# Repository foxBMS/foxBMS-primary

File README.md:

# foxBMS 

foxBMS is a free, open and flexible development environment to design battery
management systems. It is the first modular open source BMS development
platform.

## foxBMS Project Setup
The foxBMS project consists of several repositories.

The foxConda-installer repository contains the installer for the foxConda
environment. This environment provides all the tools necessary to generate the
documentation, compile the code for the MCUs and flash the generated binaries on
the MCUs (e.g., Python, git, GCC).

The starting point to get foxBMS is the foxBMS-setup
repository (https://github.com/foxBMS/foxBMS-setup), which contains
the general setup files for the foxBMS project. It includes a setup script
(bootstrap.py) which clones all the other needed repositories. The needed
documentation will be generated automatically after these repositories have been
cloned. The generated documentation is found in the directory ./build.
After the bootstrap step, the top project directory (foxBMS-setup) structure
looks like this:

 - foxBMS-setup <dir>
  - .git <dir> *
  - build <dir>
  - foxBMS-documentation <dir>
  - foxBMS-hardware <dir>
  - foxBMS-primary <dir>
  - foxBMS-secondary <dir>
  - foxBMS-tools <dir>
  - FreeRTOS <dir>
  - hal <dir>
  - .gitignore <file> *
  - bootstrap.py <file>
  - build.py <file>
  - CHANGELOG.md <file>
  - clean.py <file>
  - LICENSE.md <file>
  - README.md <file>
  - wscript <file>

* Directories and files with starting full stop are hidden in Windows in default
configuration.

There is a help available by running "python bootstrap.py -h".

## foxBMS Repositories

The foxConda-installer and foxBMS-setup repositories have already been described.

foxBMS is made out of two Microcontroller Units (MCU), named primary and
secondary. The C code for the primary MCU is found in the repository
foxBMS-primary (https://github.com/foxBMS/foxBMS-primary). The C code for the
secondary MCU is found in the repository foxBMS-secondary
(https://github.com/foxBMS/foxBMS-secondary). The Doxygen documentation is
generated from these sources into ./build/primary/doxygen/html and
./build/secondary/doxygen/html respectively. The main file is in both cases
index.html.

The layout and schematic files for the foxBMS hardware are found in the
foxBMS-hardware repository (https://github.com/foxBMS/foxBMS-hardware).

The Hardware Abstraction Layer (hal) for foxBMS is found in the hal-repository
(https://github.com/foxBMS/hal.) The real time operating system (FreeRTOS) for
foxBMS is found in the FreeRTOS-repository (https://github.com/foxBMS/FreeRTOS.)

The tools needed for foxBMS are in the foxBMS-tools-repository
(https://github.com/foxBMS/foxBMS-tools.)

The general documentation files for the foxBMS project are found in the
foxBMS-documentation repository
(https://github.com/foxBMS/foxBMS-documentation). The sphinx documentation is
found in foxBMS-documentation/doc/sphinx while the Doxygen documentation
configuration is found in foxBMS-documentation/doc/doxygen. The Doxygen
documentation itself is found in the software sources of the primary and
secondary microcontroller. The general documentation, rendered from the sphinx
sources is found in ./build/sphinx/foxBMS-documentation/doc/sphinx/html. The
main file is index.html

A generated version of the Sphinx documentation can be found at
http://foxbms.readthedocs.io/. It explains the structure of the
foxBMS hardware, how to install the foxConda environment and how to use foxConda
to compile and flash the sources.

## Building the Sources
For building the software, open a shell and type "python build.py -h". All
available build options will be displayed. The top build directory is ./build.

## Cleaning the ./build-Directory
For cleaning instructions open a shell and type "python clean.py -h". All
available cleaning options will be displayed.

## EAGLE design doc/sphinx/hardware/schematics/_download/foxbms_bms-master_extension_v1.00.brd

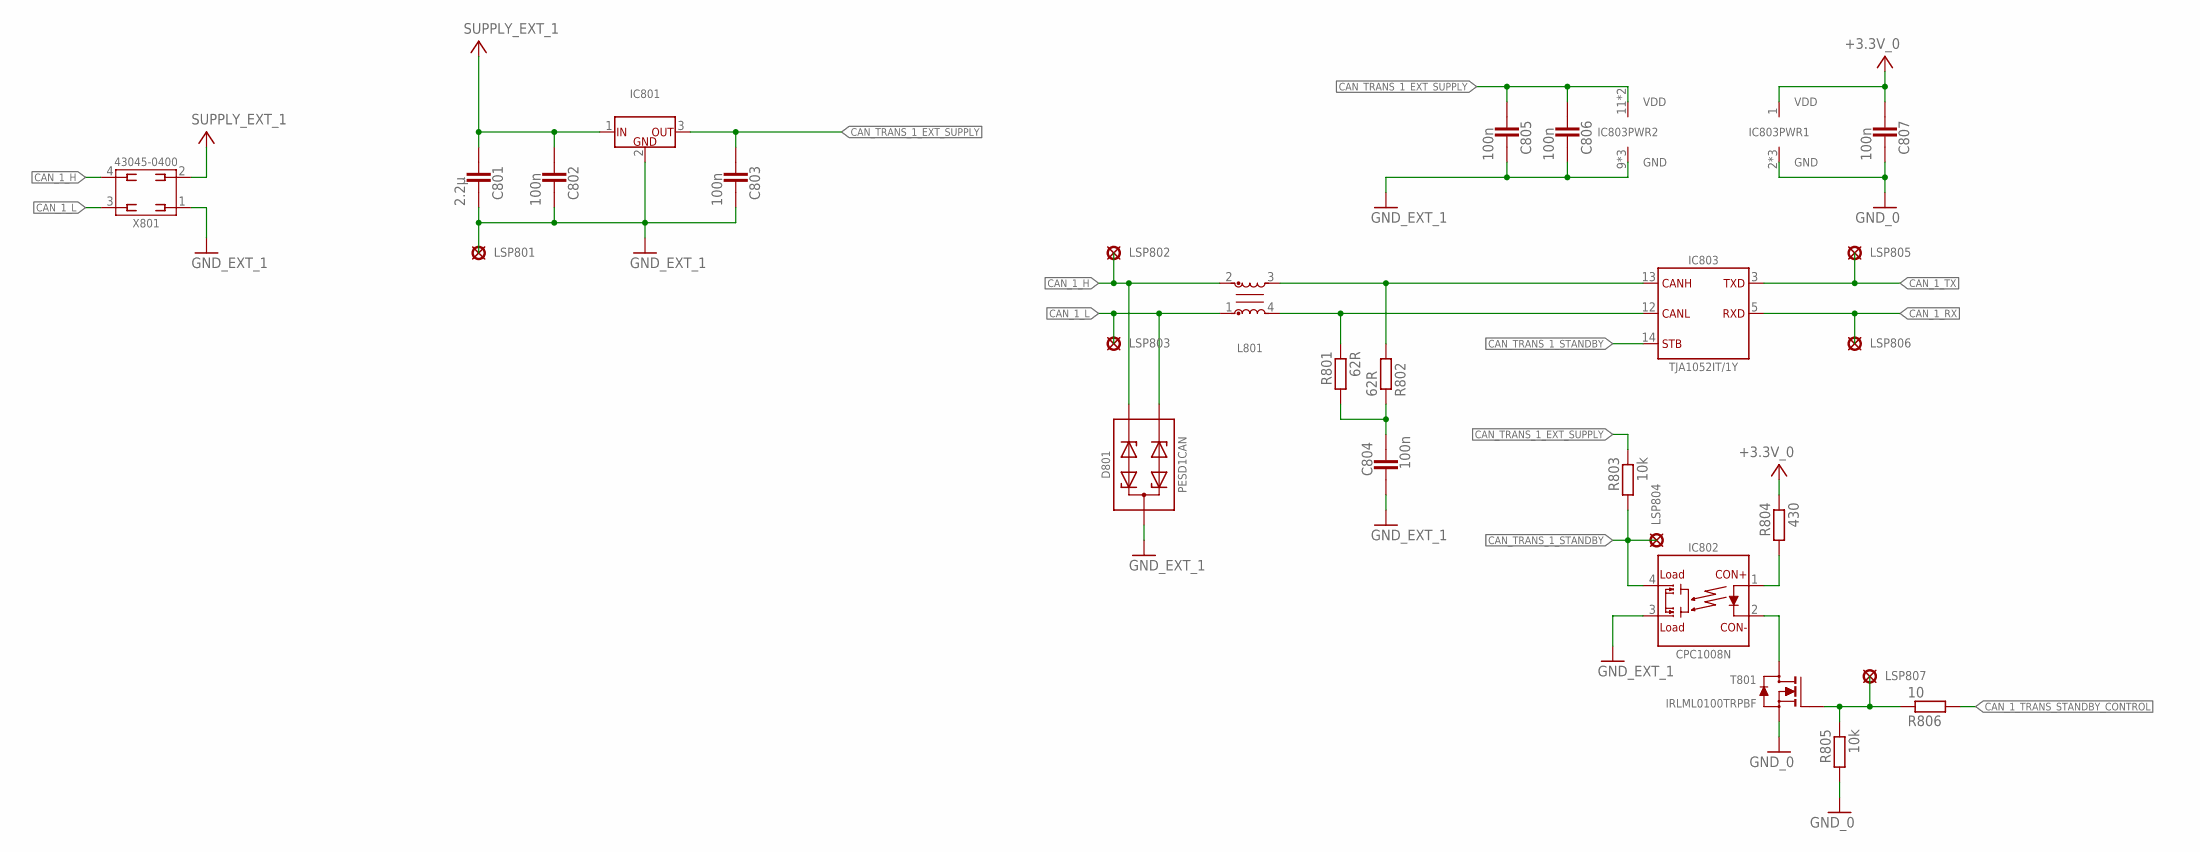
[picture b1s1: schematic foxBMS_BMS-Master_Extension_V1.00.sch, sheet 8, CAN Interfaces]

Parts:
C801: 2.2µ; 0603
C802, C803, C804, C805, C806, C807: 100n; 0603
D801: PESD1CAN; D_SMD_SOT23_(TO-236AB)_R_NXP_REV01
IC801: KA7805ERTF; IC_SMD_TO-252_(D-PAK)_R_FAIRCHILD_REV01
IC802: CPC1008N; K_SMD_SOP-4_R_IXYS_REV01
IC803: TJA1052IT/1Y; IC_SMD_SO16_(SOT162-1)_R_NXP_REV01
L801: B82789C0513N002; L_SMD_FILTER_HF_R_EPCOS_SIMDAD_1812_REV01
LSP801, LSP802, LSP803, LSP804, LSP805, LSP806, LSP807: PAD_2.0X1.5MM; PAD2.0X1.5MM
R801, R802: 62R; 0603
R803, R805: 10k; 0603
R804: 430; 0603
R806: 10; 0603
T801: IRLML0100TRPBF; V_SMD_SOT-23_(TO-236AB)_R_IR_REV01
X801: 43045-0400_MOLEX_4PIN; X_TH_MOLEX_43045-0400_R_REV01

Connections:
+3.3V_0: C807.2, IC803.1 (VDD), R804.1; also elsewhere on the board
CAN_1_H: D801.1, L801.2, LSP802.P$1, X801.4
CAN_1_L: D801.2, L801.1, LSP803.P$1, X801.3
CAN_1_RX: IC803.5 (RXD), LSP806.P$1; also elsewhere on the board
CAN_1_TRANS_STANDBY_CONTROL: R806.2; also elsewhere on the board
CAN_1_TX: IC803.3 (TXD), LSP805.P$1; also elsewhere on the board
CAN_L_INT1: IC803.12 (CANL), L801.4, R801.1
CAN_SPLIT1: C804.1, R801.2, R802.1
CAN_TRANS_1_EXT_SUPPLY: C803.2, C805.2, C806.2, IC801.3 (OUT), IC803.11 (VDD), IC803.16 (VDD), R803.1
CAN_TRANS_1_STANDBY: IC802.4, IC803.14 (STB), LSP804.P$1, R803.2
GND_0: C807.1, IC803.2 (GND), IC803.7 (GND), IC803.8 (GND), R805.2, T801.2 (S); also elsewhere on the board
GND_EXT_1: C801.1, C802.1, C803.1, C804.2, C805.1, C806.1, D801.3, IC801.2 (GND), IC802.3, IC803.9 (GND), IC803.10 (GND), IC803.15 (GND), LSP801.P$1, X801.1
unnamed: IC803.13 (CANH), L801.3, R802.2
unnamed: IC802.2 (CON-), T801.3 (D)
unnamed: IC802.1 (CON+), R804.2
unnamed: LSP807.P$1, R805.1, R806.1, T801.1 (G)
SUPPLY_EXT_1: C801.2, C802.2, IC801.1 (IN), X801.2

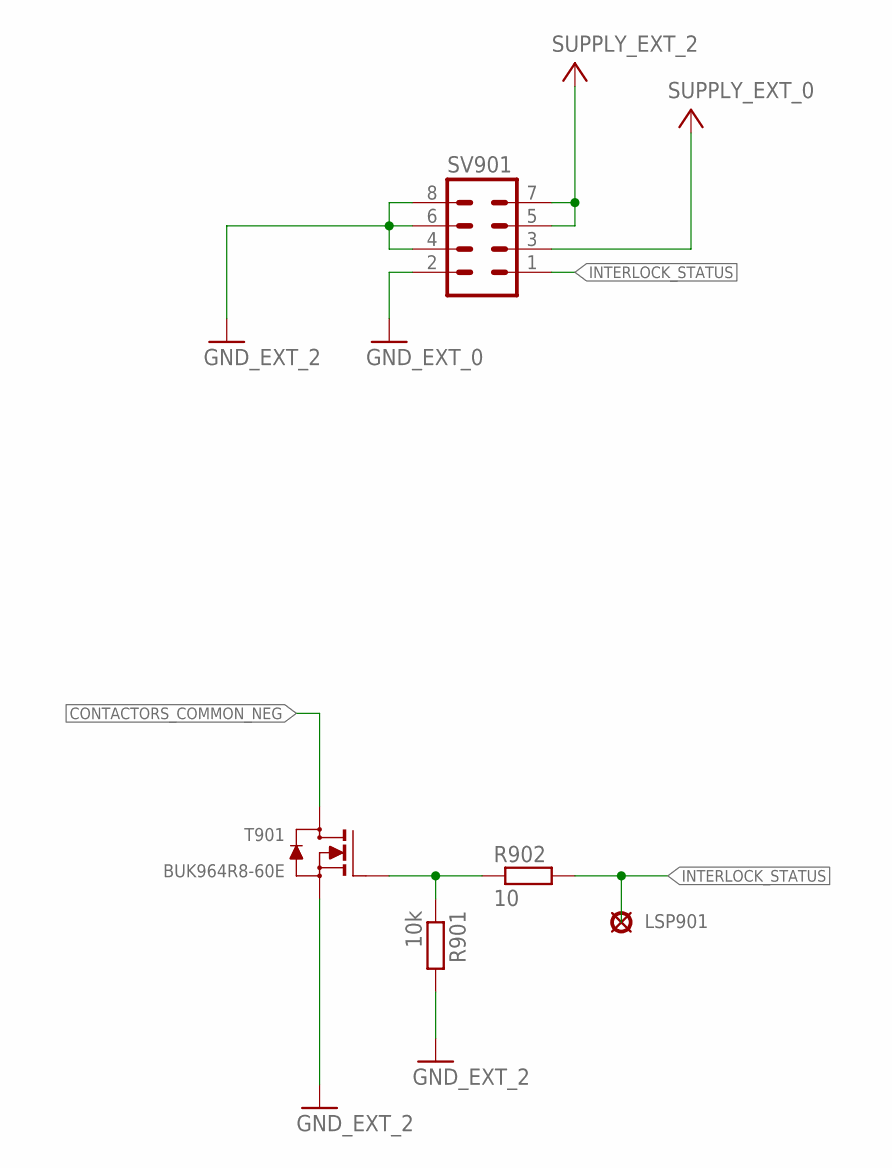
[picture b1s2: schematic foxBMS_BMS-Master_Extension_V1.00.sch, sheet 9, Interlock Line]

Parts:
LSP901: PAD_2.0X1.5MM; PAD2.0X1.5MM
R901: 10k; 0603
R902: 10; 0603
SV901: MA04-2
T901: BUK964R8-60E; V_SMD_TO-263_(D²PAK)_R_NXP_REV01

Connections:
CONTACTORS_COMMON_NEG: T901.2 (D); also elsewhere on the board
GND_EXT_0: SV901.2; also elsewhere on the board
GND_EXT_2: R901.2, SV901.4, SV901.6, SV901.8, T901.3 (S); also elsewhere on the board
INTERLOCK_STATUS: LSP901.P$1, R902.2, SV901.1
unnamed: R901.1, R902.1, T901.1 (G)
SUPPLY_EXT_0: SV901.3; also elsewhere on the board
SUPPLY_EXT_2: SV901.5, SV901.7; also elsewhere on the board

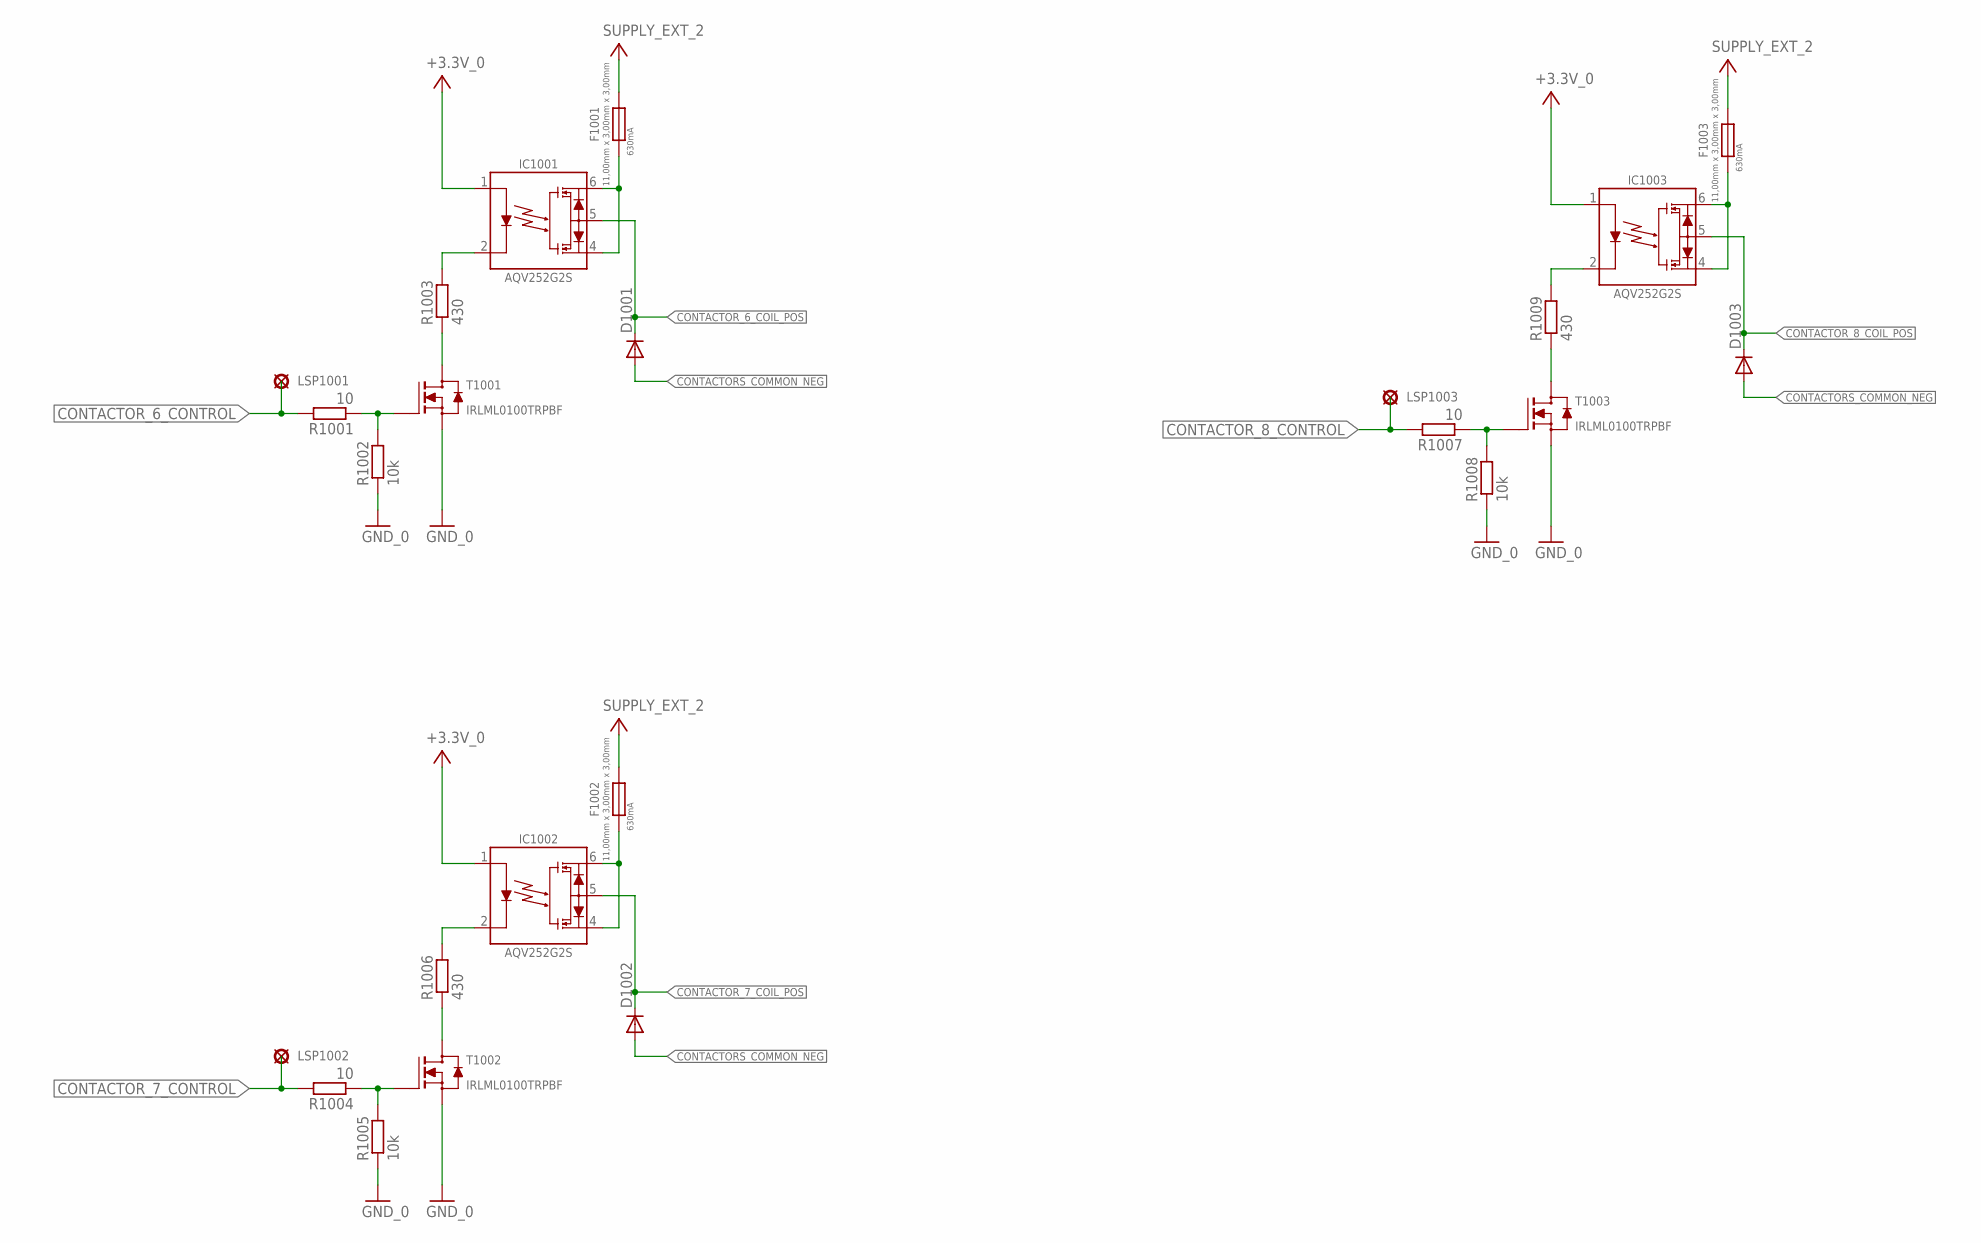
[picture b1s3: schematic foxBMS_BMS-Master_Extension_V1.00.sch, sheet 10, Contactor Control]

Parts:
D1001, D1002, D1003: DIODE-DO214BA; DO214BA
F1001, F1002, F1003: 630MA_UMT; F_SMD_11,00MMX3,00MMX3,00MM_(UMT)_R_SCHURTER_REV01
IC1001, IC1002, IC1003: AQV252G2S; K_SMD_SOP-6_R_PANASONIC_REV01
LSP1001, LSP1002, LSP1003: PAD_2.0X1.5MM; PAD2.0X1.5MM
R1001, R1004, R1007: 10; 0603
R1002, R1005, R1008: 10k; 0603
R1003, R1006, R1009: 430; 0603
T1001, T1002, T1003: IRLML0100TRPBF; V_SMD_SOT-23_(TO-236AB)_R_IR_REV01

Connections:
+3.3V_0: IC1001.1, IC1002.1, IC1003.1; also elsewhere on the board
CONTACTORS_COMMON_NEG: D1001.A, D1002.A, D1003.A; also elsewhere on the board
CONTACTOR_6_COIL_POS: D1001.C, IC1001.5; also elsewhere on the board
CONTACTOR_6_CONTROL: LSP1001.P$1, R1001.2; also elsewhere on the board
CONTACTOR_7_COIL_POS: D1002.C, IC1002.5; also elsewhere on the board
CONTACTOR_7_CONTROL: LSP1002.P$1, R1004.2; also elsewhere on the board
CONTACTOR_8_COIL_POS: D1003.C, IC1003.5; also elsewhere on the board
CONTACTOR_8_CONTROL: LSP1003.P$1, R1007.2; also elsewhere on the board
GND_0: R1002.1, R1005.1, R1008.1, T1001.2 (S), T1002.2 (S), T1003.2 (S); also elsewhere on the board
unnamed: R1003.1, T1001.3 (D)
unnamed: R1006.1, T1002.3 (D)
unnamed: R1009.1, T1003.3 (D)
unnamed: F1001.1, IC1001.4, IC1001.6
unnamed: F1002.1, IC1002.4, IC1002.6
unnamed: F1003.1, IC1003.4, IC1003.6
unnamed: IC1001.2, R1003.2
unnamed: R1001.1, R1002.2, T1001.1 (G)
unnamed: IC1002.2, R1006.2
unnamed: R1004.1, R1005.2, T1002.1 (G)
unnamed: IC1003.2, R1009.2
unnamed: R1007.1, R1008.2, T1003.1 (G)
SUPPLY_EXT_2: F1001.2, F1002.2, F1003.2; also elsewhere on the board

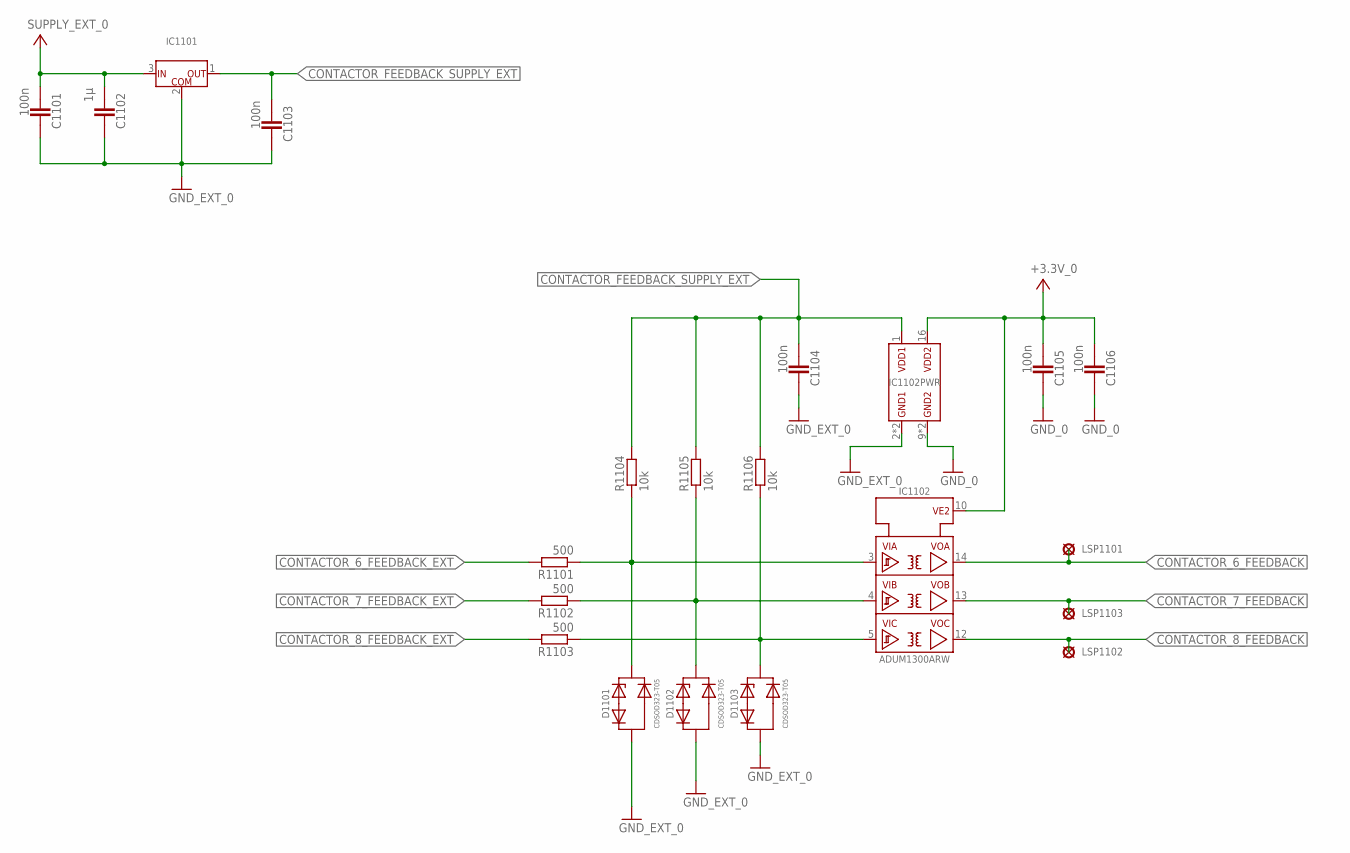
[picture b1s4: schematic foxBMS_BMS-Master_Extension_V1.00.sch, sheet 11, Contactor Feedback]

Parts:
C1101, C1103, C1104, C1105, C1106: 100n; 0603
C1102: 1µ; 0603
D1101, D1102, D1103: CDSOD323-T05; D_SMD_SOD323_(SC-76)_R_BOURNS_REV01
IC1101: UA78L05ACPK; IC_SMD_SOT-89_(SC-62/TO-243)_(R-PSSO-F3)_R_TI_REV01
IC1102: ADUM1300ARW; IC_SMD_SOIC-16_(JEDEC_MS-013-AA)_R_ANALOG_REV01
LSP1101, LSP1102, LSP1103: PAD_2.0X1.5MM; PAD2.0X1.5MM
R1101, R1102, R1103: 500; 0603
R1104, R1105, R1106: 10k; 0603

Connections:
+3.3V_0: C1105.1, C1106.1, IC1102.10 (VE2), IC1102.16 (VDD2); also elsewhere on the board
CONTACTOR_6_FEEDBACK: IC1102.14 (VOA), LSP1101.P$1; also elsewhere on the board
CONTACTOR_6_FEEDBACK_EXT: R1101.2; also elsewhere on the board
CONTACTOR_7_FEEDBACK: IC1102.13 (VOB), LSP1103.P$1; also elsewhere on the board
CONTACTOR_7_FEEDBACK_EXT: R1102.2; also elsewhere on the board
CONTACTOR_8_FEEDBACK: IC1102.12 (VOC), LSP1102.P$1; also elsewhere on the board
CONTACTOR_8_FEEDBACK_EXT: R1103.2; also elsewhere on the board
CONTACTOR_FEEDBACK_SUPPLY_EXT: C1103.1, C1104.1, IC1101.1 (OUT), IC1102.1 (VDD1), R1104.2, R1105.2, R1106.2
GND_0: C1105.2, C1106.2, IC1102.9 (GND2), IC1102.15 (GND2); also elsewhere on the board
GND_EXT_0: C1101.2, C1102.2, C1103.2, C1104.2, D1101.A, D1102.A, D1103.A, IC1101.2 (COM), IC1102.2 (GND1), IC1102.8 (GND1); also elsewhere on the board
unnamed: D1101.C, IC1102.3 (VIA), R1101.1, R1104.1
unnamed: D1102.C, IC1102.4 (VIB), R1102.1, R1105.1
unnamed: D1103.C, IC1102.5 (VIC), R1103.1, R1106.1
SUPPLY_EXT_0: C1101.1, C1102.1, IC1101.3 (IN); also elsewhere on the board

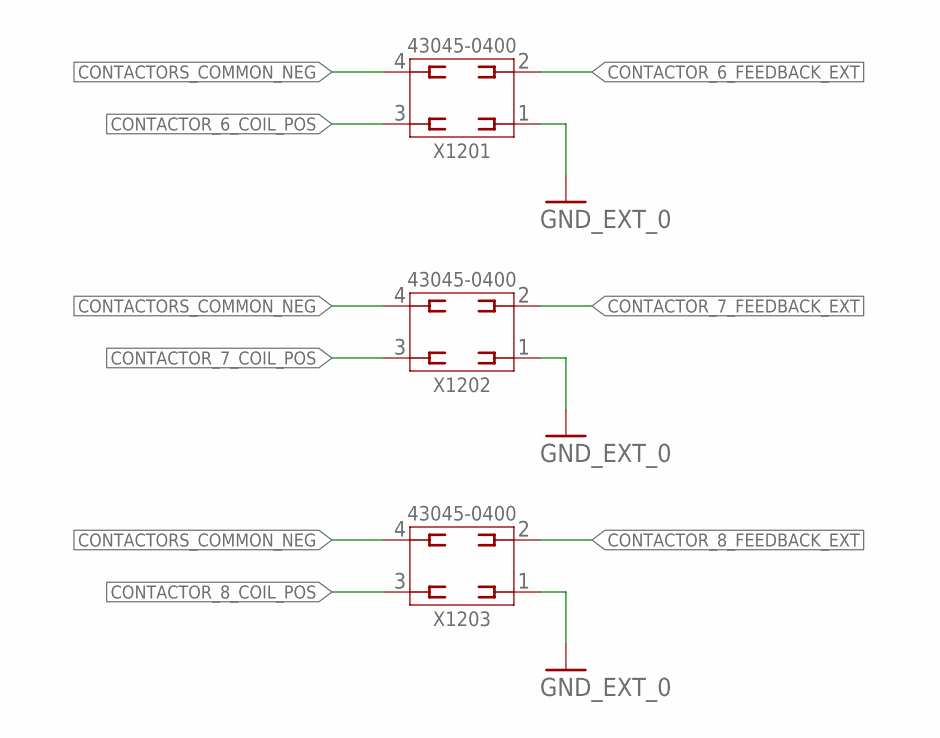
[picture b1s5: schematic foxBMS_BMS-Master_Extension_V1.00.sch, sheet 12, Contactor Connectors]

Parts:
X1201, X1202, X1203: 43045-0400_MOLEX_4PIN; X_TH_MOLEX_43045-0400_R_REV01

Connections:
CONTACTORS_COMMON_NEG: X1201.4, X1202.4, X1203.4; also elsewhere on the board
CONTACTOR_6_COIL_POS: X1201.3; also elsewhere on the board
CONTACTOR_6_FEEDBACK_EXT: X1201.2; also elsewhere on the board
CONTACTOR_7_COIL_POS: X1202.3; also elsewhere on the board
CONTACTOR_7_FEEDBACK_EXT: X1202.2; also elsewhere on the board
CONTACTOR_8_COIL_POS: X1203.3; also elsewhere on the board
CONTACTOR_8_FEEDBACK_EXT: X1203.2; also elsewhere on the board
GND_EXT_0: X1201.1, X1202.1, X1203.1; also elsewhere on the board

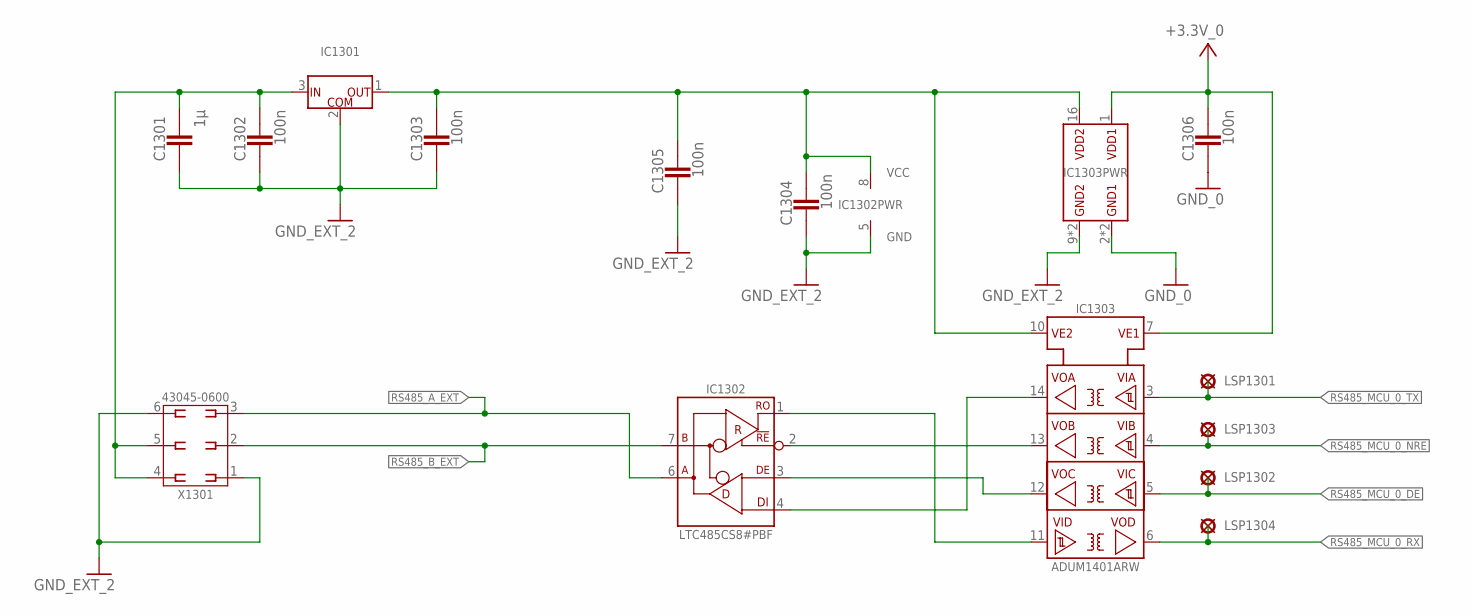
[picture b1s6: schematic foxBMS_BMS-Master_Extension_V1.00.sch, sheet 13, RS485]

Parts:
C1301: 1µ; 0603
C1302, C1303, C1304, C1305, C1306: 100n; 0603
IC1301: UA78L05ACPK; IC_SMD_SOT-89_(SC-62/TO-243)_(R-PSSO-F3)_R_TI_REV01
IC1302: LTC485CS8#PBF; IC_SMD_SOIC-8_(S8_REV_G)_R_LINEAR_REV01
IC1303: ADUM1401ARW; IC_SMD_SOIC-16_(JEDEC_MS-013-AA)_R_ANALOG_REV01
LSP1301, LSP1302, LSP1303, LSP1304: PAD_2.0X1.5MM; PAD2.0X1.5MM
X1301: 43045-0600_MOLEX_6PIN; X_TH_MOLEX_43045-0600_R_REV01

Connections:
+3.3V_0: C1306.1, IC1303.1 (VDD1), IC1303.7 (VE1); also elsewhere on the board
GND_0: C1306.2, IC1303.2 (GND1), IC1303.8 (GND1); also elsewhere on the board
GND_EXT_2: C1301.2, C1302.2, C1303.2, C1304.2, C1305.2, IC1301.2 (COM), IC1302.5 (GND), IC1303.9 (GND2), IC1303.15 (GND2), X1301.1, X1301.6; also elsewhere on the board
unnamed: C1301.1, C1302.1, IC1301.3 (IN), X1301.4, X1301.5
unnamed: IC1302.1 (RO), IC1303.11 (VID)
unnamed: IC1302.2 (!RE), IC1303.13 (VOB)
unnamed: IC1302.3 (DE), IC1303.12 (VOC)
unnamed: IC1302.4 (DI), IC1303.14 (VOA)
unnamed: C1303.1, C1304.1, C1305.1, IC1301.1 (OUT), IC1302.8 (VCC), IC1303.10 (VE2), IC1303.16 (VDD2)
RS485_A_EXT: IC1302.6 (A), X1301.3
RS485_B_EXT: IC1302.7 (B), X1301.2
RS485_MCU_0_DE: IC1303.5 (VIC), LSP1302.P$1; also elsewhere on the board
RS485_MCU_0_NRE: IC1303.4 (VIB), LSP1303.P$1; also elsewhere on the board
RS485_MCU_0_RX: IC1303.6 (VOD), LSP1304.P$1; also elsewhere on the board
RS485_MCU_0_TX: IC1303.3 (VIA), LSP1301.P$1; also elsewhere on the board

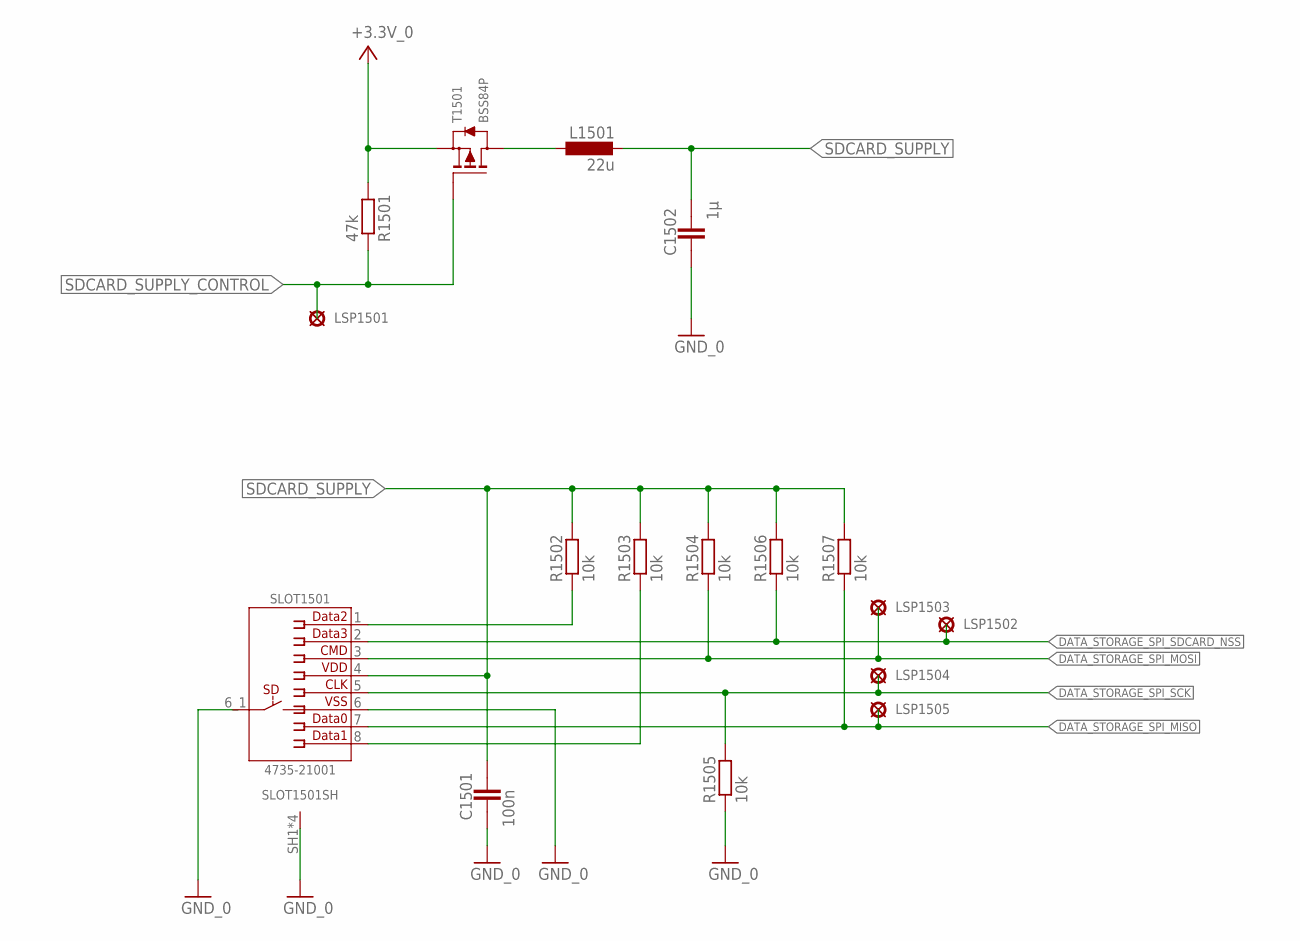
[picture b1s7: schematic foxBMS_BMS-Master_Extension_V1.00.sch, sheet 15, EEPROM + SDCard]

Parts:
C1501: 100n; 0603
C1502: 1µ; 0603
L1501: 22u; 0805
LSP1501, LSP1502, LSP1503, LSP1504, LSP1505: PAD_2.0X1.5MM; PAD2.0X1.5MM
R1501: 47k; 0603
R1502, R1503, R1504, R1505, R1506, R1507: 10k; 0603
SLOT1501: MICRO_SD; X_SMD_MICRO-SD-4735-21001_R_MOLEX_REV01
T1501: BSS84P; V_SMD_SOT23_(TO-236AB)_R_INFINEON_REV01

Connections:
+3.3V_0: R1501.2, T1501.2 (S); also elsewhere on the board
DATA_STORAGE_SPI_MISO: LSP1505.P$1, R1507.1, SLOT1501.7; also elsewhere on the board
DATA_STORAGE_SPI_MOSI: LSP1503.P$1, R1504.1, SLOT1501.3; also elsewhere on the board
DATA_STORAGE_SPI_SCK: LSP1504.P$1, R1505.2, SLOT1501.5; also elsewhere on the board
DATA_STORAGE_SPI_SDCARD_NSS: LSP1502.P$1, R1506.1, SLOT1501.2; also elsewhere on the board
GND_0: C1501.1, C1502.2, R1505.1, SLOT1501.6, SLOT1501.6_1 (9), SLOT1501.SH1 (SH), SLOT1501.SH2 (SH), SLOT1501.SH3 (SH), SLOT1501.SH5 (SH); also elsewhere on the board
unnamed: L1501.2, T1501.3 (D)
unnamed: R1502.1, SLOT1501.1
unnamed: R1503.1, SLOT1501.8
SDCARD_SUPPLY: C1501.2, C1502.1, L1501.1, R1502.2, R1503.2, R1504.2, R1506.2, R1507.2, SLOT1501.4
SDCARD_SUPPLY_CONTROL: LSP1501.P$1, R1501.1, T1501.1 (G); also elsewhere on the board

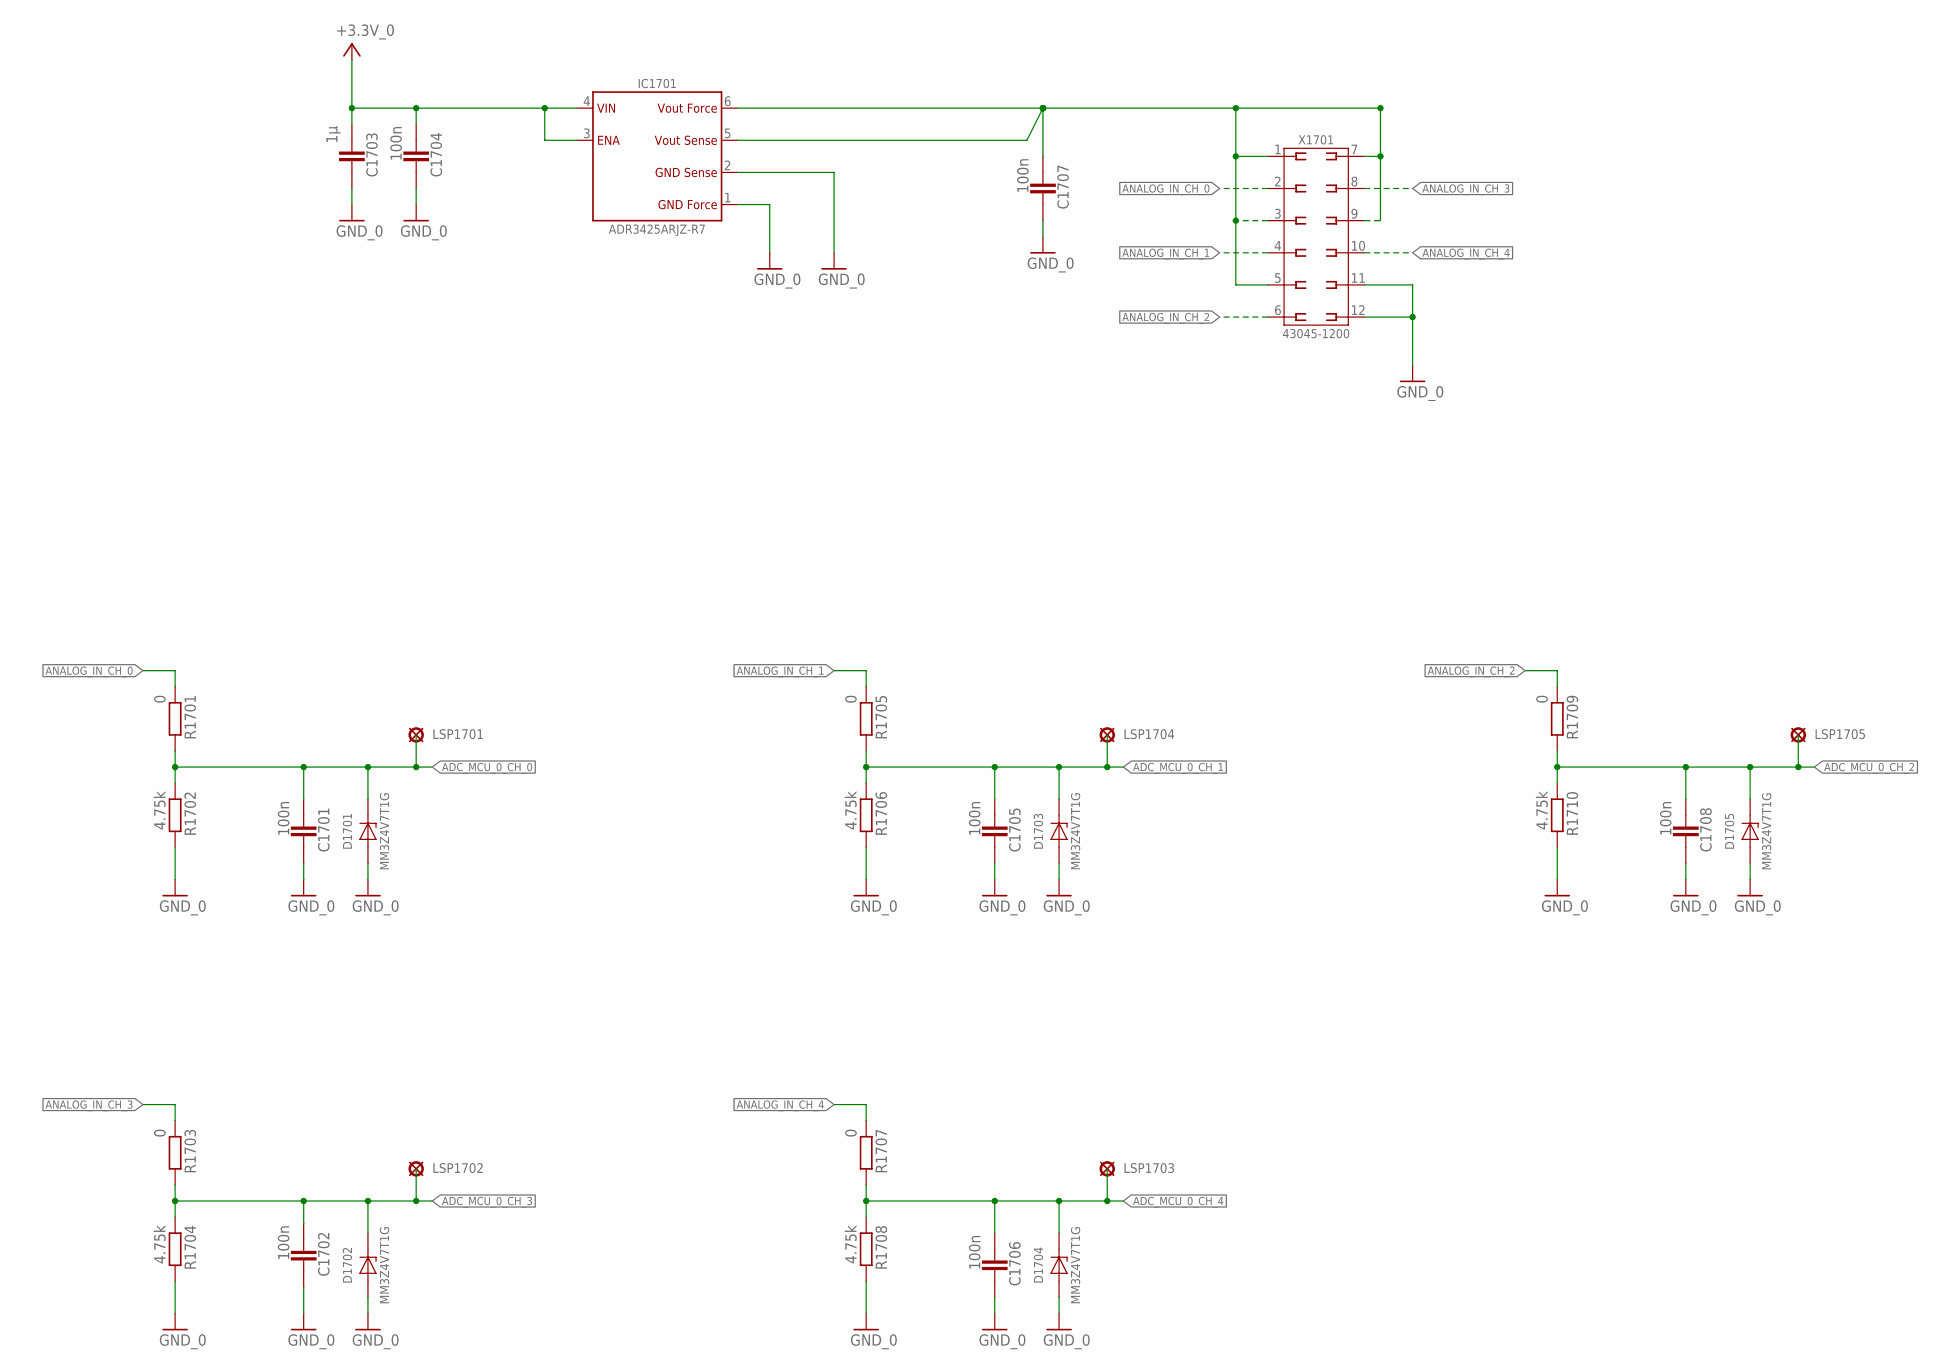
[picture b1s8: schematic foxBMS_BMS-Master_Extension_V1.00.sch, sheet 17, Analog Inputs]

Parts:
C1701, C1702, C1704, C1705, C1706, C1707, C1708: 100n; 0603
C1703: 1µ; 0603
D1701, D1702, D1703, D1704, D1705: MM3Z3V3ST1G; D_SMD_SOD323_(SC-76)_R_ON_REV01
IC1701: ADR3425ARJZ; IC_SMD_SOT23-6_(MO-178-AB)_R_AD_REV01
LSP1701, LSP1702, LSP1703, LSP1704, LSP1705: PAD_2.0X1.5MM; PAD2.0X1.5MM
R1701, R1703, R1705, R1707, R1709: 0; 0603
R1702, R1704, R1706, R1708, R1710: 4.75k; 0603
X1701: 43045-1200_MOLEX_12PIN; X_TH_MOLEX_43045-1200_R_REV01

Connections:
+3.3V_0: C1703.1, C1704.1, IC1701.3 (ENABLE), IC1701.4 (VIN); also elsewhere on the board
ADC_MCU_0_CH_0: C1701.1, D1701.C, LSP1701.P$1, R1701.2, R1702.1; also elsewhere on the board
ADC_MCU_0_CH_1: C1705.1, D1703.C, LSP1704.P$1, R1705.2, R1706.1; also elsewhere on the board
ADC_MCU_0_CH_2: C1708.1, D1705.C, LSP1705.P$1, R1709.2, R1710.1; also elsewhere on the board
ADC_MCU_0_CH_3: C1702.1, D1702.C, LSP1702.P$1, R1703.2, R1704.1; also elsewhere on the board
ADC_MCU_0_CH_4: C1706.1, D1704.C, LSP1703.P$1, R1707.2, R1708.1; also elsewhere on the board
ANALOG_IN_CH_0: R1701.1, X1701.2
ANALOG_IN_CH_1: R1705.1, X1701.4
ANALOG_IN_CH_2: R1709.1, X1701.6
ANALOG_IN_CH_3: R1703.1, X1701.8
ANALOG_IN_CH_4: R1707.1, X1701.10
GND_0: C1701.2, C1702.2, C1703.2, C1704.2, C1705.2, C1706.2, C1707.2, C1708.2, D1701.A, D1702.A, D1703.A, D1704.A, D1705.A, IC1701.1 (GND_FORCE), IC1701.2 (GND_SENSE), R1702.2, R1704.2, R1706.2, R1708.2, R1710.2, X1701.11, X1701.12; also elsewhere on the board
unnamed: C1707.1, IC1701.5 (VOUT_SENSE), IC1701.6 (VOUT_FORCE), X1701.1, X1701.3, X1701.5, X1701.7, X1701.9

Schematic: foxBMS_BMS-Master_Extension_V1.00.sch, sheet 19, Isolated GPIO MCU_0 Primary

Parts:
C1901, C1903, C1904, C1905, C1906, C1907: 100n; 0603
C1902: 1µ; 0603
D1901, D1902, D1903, D1904: CDSOD323-T05; D_SMD_SOD323_(SC-76)_R_BOURNS_REV01
IC1901: UA78L05ACPK; IC_SMD_SOT-89_(SC-62/TO-243)_(R-PSSO-F3)_R_TI_REV01
IC1902, IC1903: ADUM1402ARW; IC_SMD_SOIC-16_(JEDEC_MS-013-AA)_R_ANALOG_REV01
LSP1901, LSP1902, LSP1903, LSP1904, LSP1905, LSP1906, LSP1907, LSP1908: PAD_2.0X1.5MM; PAD2.0X1.5MM
R1901, R1902, R1905, R1906: 500; 0603
R1903, R1904, R1907, R1908: 10k; 0603
X1901: 43045-1000_MOLEX_10PIN; X_TH_MOLEX_43045-1000_R_REV01

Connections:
+3.3V_0: C1905.1, C1907.1, IC1902.10 (VE2), IC1902.16 (VDD2), IC1903.10 (VE2), IC1903.16 (VDD2); also elsewhere on the board
GND_0: C1905.2, C1907.2, IC1902.9 (GND2), IC1902.15 (GND2), IC1903.9 (GND2), IC1903.15 (GND2); also elsewhere on the board
GND_EXT_0: C1901.2, C1902.2, C1903.2, C1904.2, C1906.2, D1901.A, D1902.A, D1903.A, D1904.A, IC1901.2 (COM), IC1902.2 (GND1), IC1902.8 (GND1), IC1903.2 (GND1), IC1903.8 (GND1), R1903.1, R1904.1, R1907.1, R1908.1, X1901.9, X1901.10; also elsewhere on the board
ISO_GPIO_MCU_0_IN_0: IC1902.14 (VOA), LSP1903.P$1; also elsewhere on the board
ISO_GPIO_MCU_0_IN_0_EXT: R1904.2, X1901.5
ISO_GPIO_MCU_0_IN_1: IC1902.13 (VOB), LSP1901.P$1; also elsewhere on the board
ISO_GPIO_MCU_0_IN_1_EXT: IC1902.4 (VIB), R1903.2, X1901.6
ISO_GPIO_MCU_0_IN_2: IC1903.14 (VOA), LSP1905.P$1; also elsewhere on the board
ISO_GPIO_MCU_0_IN_2_EXT: IC1903.3 (VIA), R1908.2, X1901.7
ISO_GPIO_MCU_0_IN_3: IC1903.13 (VOB), LSP1907.P$1; also elsewhere on the board
ISO_GPIO_MCU_0_IN_3_EXT: IC1903.4 (VIB), R1907.2, X1901.8
ISO_GPIO_MCU_0_OUT_0: IC1902.12 (VIC), LSP1904.P$1; also elsewhere on the board
ISO_GPIO_MCU_0_OUT_0_EXT: R1901.2, X1901.1
ISO_GPIO_MCU_0_OUT_1: IC1902.11 (VID), LSP1902.P$1; also elsewhere on the board
ISO_GPIO_MCU_0_OUT_1_EXT: R1902.2, X1901.2
ISO_GPIO_MCU_0_OUT_2: IC1903.12 (VIC), LSP1906.P$1; also elsewhere on the board
ISO_GPIO_MCU_0_OUT_2_EXT: R1905.2, X1901.3
ISO_GPIO_MCU_0_OUT_3: IC1903.11 (VID), LSP1908.P$1; also elsewhere on the board
ISO_GPIO_MCU_0_OUT_3_EXT: R1906.2, X1901.4
ISO_GPIO_SUPPLY: C1903.1, C1904.1, C1906.1, IC1901.1 (OUT), IC1902.1 (VDD1), IC1902.7 (VE1), IC1903.1 (VDD1), IC1903.7 (VE1)
unnamed: D1901.C, IC1902.5 (VOC), R1901.1
unnamed: D1902.C, IC1902.6 (VOD), R1902.1
unnamed: D1903.C, IC1903.5 (VOC), R1905.1
unnamed: D1904.C, IC1903.6 (VOD), R1906.1
SUPPLY_EXT_0: C1901.1, C1902.1, IC1901.3 (IN); also elsewhere on the board

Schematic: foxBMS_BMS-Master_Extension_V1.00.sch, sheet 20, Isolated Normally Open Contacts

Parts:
D2001, D2002, D2003, D2004, D2005, D2006: DIODE-DO214BA; DO214BA
IC2001, IC2002, IC2003, IC2004, IC2005, IC2006: AQV25G2S; SOP06
LSP2001, LSP2002, LSP2003, LSP2004, LSP2005, LSP2006: PAD_2.0X1.5MM; PAD2.0X1.5MM
R2001, R2002, R2007, R2008, R2013, R2014: 10; 0603
R2003, R2004, R2009, R2010, R2015, R2016: 10k; 0603
R2005, R2006, R2011, R2012, R2017, R2018: 430; 0603
T2001, T2002, T2003, T2004, T2005, T2006: IRLML0100TRPBF; V_SMD_SOT-23_(TO-236AB)_R_IR_REV01
X2001: 43045-1200_MOLEX_12PIN; X_TH_MOLEX_43045-1200_R_REV01

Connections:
+3.3V_0: IC2001.1 (A), IC2002.1 (A), IC2003.1 (A), IC2004.1 (A), IC2005.1 (A), IC2006.1 (A); also elsewhere on the board
GND_0: R2003.1, R2004.1, R2009.1, R2010.1, R2015.1, R2016.1, T2001.2 (S), T2002.2 (S), T2003.2 (S), T2004.2 (S), T2005.2 (S), T2006.2 (S); also elsewhere on the board
ISONOC_0_CONTROL: LSP2001.P$1, R2001.2; also elsewhere on the board
ISONOC_0_NEGATIVE: D2001.A, IC2001.5 (S), X2001.7
ISONOC_0_POSITIVE: D2001.C, IC2001.4 (D1), IC2001.6 (D2), X2001.1
ISONOC_1_CONTROL: LSP2003.P$1, R2007.2; also elsewhere on the board
ISONOC_1_NEGATIVE: D2003.A, IC2003.5 (S), X2001.8
ISONOC_1_POSITIVE: D2003.C, IC2003.4 (D1), IC2003.6 (D2), X2001.2
ISONOC_2_CONTROL: LSP2005.P$1, R2013.2; also elsewhere on the board
ISONOC_2_NEGATIVE: D2005.A, IC2005.5 (S), X2001.9
ISONOC_2_POSITIVE: D2005.C, IC2005.4 (D1), IC2005.6 (D2), X2001.3
ISONOC_3_CONTROL: LSP2002.P$1, R2002.2; also elsewhere on the board
ISONOC_3_NEGATIVE: D2002.A, IC2002.5 (S), X2001.10
ISONOC_3_POSITIVE: D2002.C, IC2002.4 (D1), IC2002.6 (D2), X2001.4
ISONOC_4_CONTROL: LSP2004.P$1, R2008.2; also elsewhere on the board
ISONOC_4_NEGATIVE: D2004.A, IC2004.5 (S), X2001.11
ISONOC_4_POSITIVE: D2004.C, IC2004.4 (D1), IC2004.6 (D2), X2001.5
ISONOC_5_CONTROL: LSP2006.P$1, R2014.2; also elsewhere on the board
ISONOC_5_NEGATIVE: D2006.A, IC2006.5 (S), X2001.12
ISONOC_5_POSITIVE: D2006.C, IC2006.4 (D1), IC2006.6 (D2), X2001.6
unnamed: R2005.1, T2001.3 (D)
unnamed: R2011.1, T2003.3 (D)
unnamed: IC2003.2 (K), R2011.2
unnamed: R2017.1, T2005.3 (D)
unnamed: IC2005.2 (K), R2017.2
unnamed: R2006.1, T2002.3 (D)
unnamed: IC2002.2 (K), R2006.2
unnamed: R2012.1, T2004.3 (D)
unnamed: IC2004.2 (K), R2012.2
unnamed: R2018.1, T2006.3 (D)
unnamed: IC2006.2 (K), R2018.2
unnamed: IC2001.2 (K), R2005.2
unnamed: R2001.1, R2003.2, T2001.1 (G)
unnamed: R2007.1, R2009.2, T2003.1 (G)
unnamed: R2013.1, R2015.2, T2005.1 (G)
unnamed: R2002.1, R2004.2, T2002.1 (G)
unnamed: R2008.1, R2010.2, T2004.1 (G)
unnamed: R2014.1, R2016.2, T2006.1 (G)

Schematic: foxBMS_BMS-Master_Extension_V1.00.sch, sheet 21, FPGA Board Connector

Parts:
LSP2101, LSP2102: PAD_2.0X1.5MM; PAD2.0X1.5MM
SV2101: MA04-2

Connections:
+3.3V_0: LSP2101.P$1, SV2101.1; also elsewhere on the board
+5.0V_0: SV2101.2
GND_0: LSP2102.P$1, SV2101.5, SV2101.6; also elsewhere on the board
MCU_TO_FPGA_INTERFACE_MCU_0_CS: SV2101.8
MCU_TO_FPGA_INTERFACE_MCU_0_MISO: SV2101.3
MCU_TO_FPGA_INTERFACE_MCU_0_MOSI: SV2101.7
MCU_TO_FPGA_INTERFACE_MCU_0_SCK: SV2101.4

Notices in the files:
doc/sphinx/hardware/schematics/_download/foxbms_bms-interface_v1.00.brd:
Creative Commons
Attribution 4.0
parts and their libraries:
foxBMS_BMS-Master_V1.00_A: LICENSE: Creative Commons Attribution 4.0
